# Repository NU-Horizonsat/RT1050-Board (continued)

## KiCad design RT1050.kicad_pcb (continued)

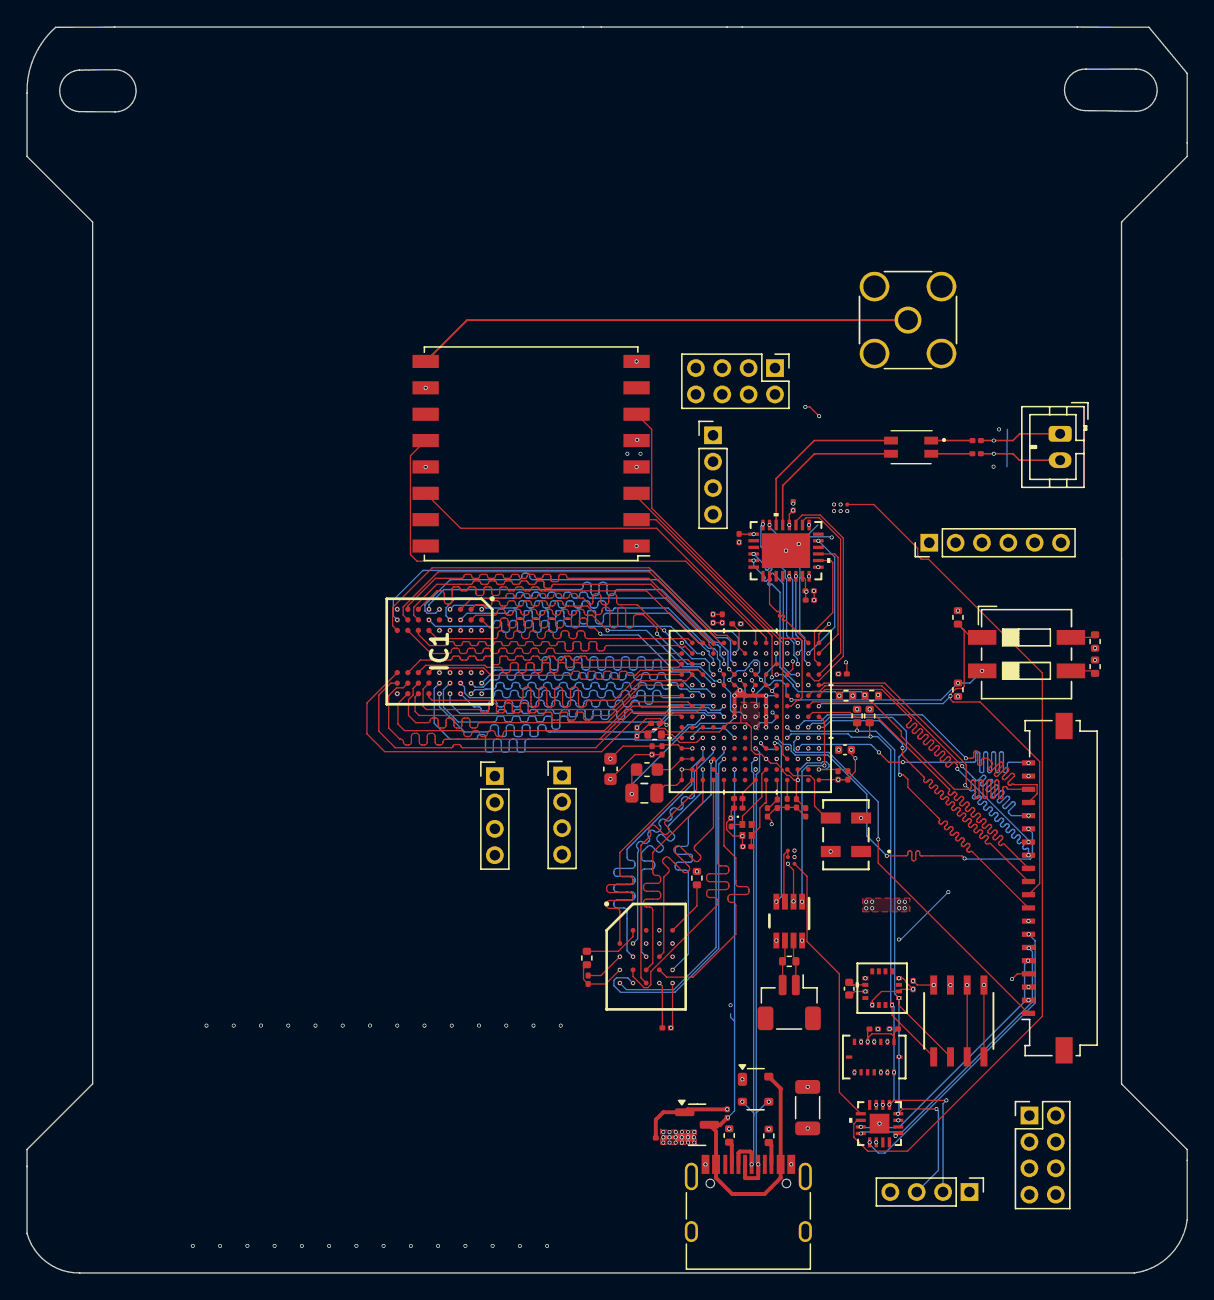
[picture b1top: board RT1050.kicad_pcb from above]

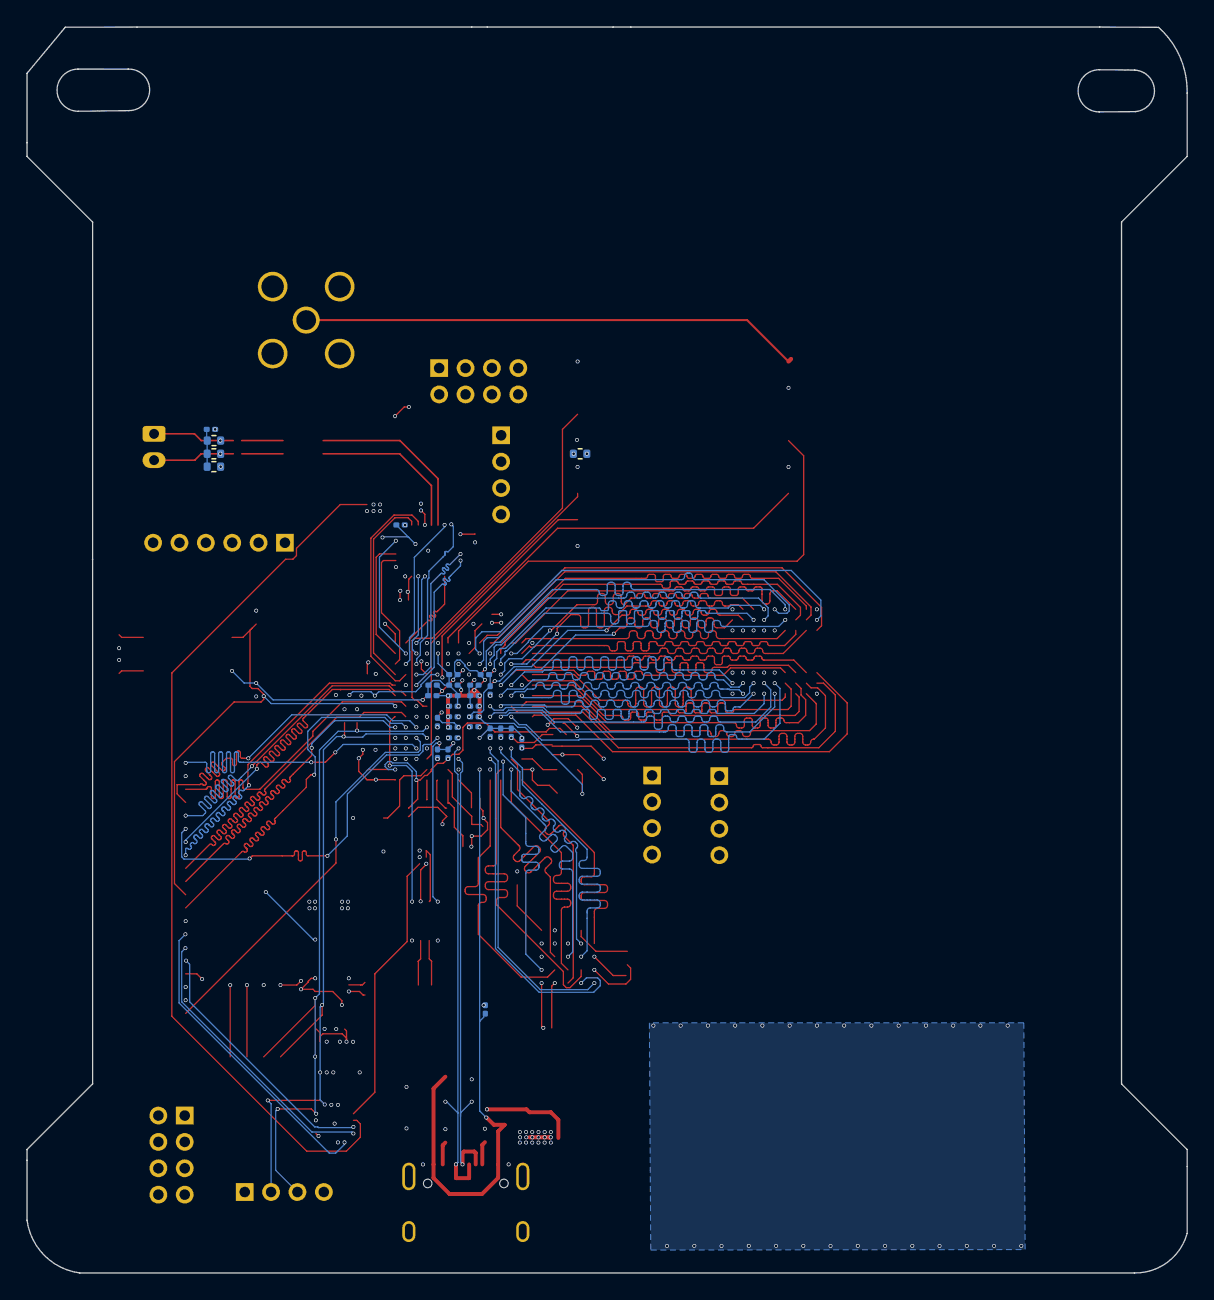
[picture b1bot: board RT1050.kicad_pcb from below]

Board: 4 copper layers, 88.0 x 94.5 mm, 112 parts (30 on the bottom side), 154 nets.

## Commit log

2024-10-18 Started RT1050 work
2024-11-06 assign pin functions and started spe
2024-11-12 finished v1
2024-11-16 added load switches
2024-12-04 save before sdram redesign
2024-12-04 quick drc fix before sdram redo
2024-12-05 SDRAM redo and finished boards
2024-12-05 added FRAM
2024-12-05 updated schem pdf
2024-12-05 quick correction
2024-12-08 cleaned up and dealt with drc
2024-12-24 quick fix
2024-12-31 Created Reference Docs and initial upload
2025-01-03 changes to board due to availability of components
